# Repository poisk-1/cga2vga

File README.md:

# CGA to VGA converter

Converts RGBI/HSYNC/VSYNC TTL signal at 15 MHz pixel clock and 640 by 200 resolution to standard VGA. Prototyped on [Arty A7-35T](https://digilent.com/reference/programmable-logic/arty-a7/reference-manual?redirect=1). Production on [Cmod A7-15T](https://digilent.com/reference/programmable-logic/cmod-a7/reference-manual) board.

## Build Top.v

    $ sbt run

## Run tests

    $ sbt test

## Vivado design for Cmod A7-15T

## TODOs

- Capture alignment configurable with push buttons;
- Design PCB around Cmod A7.

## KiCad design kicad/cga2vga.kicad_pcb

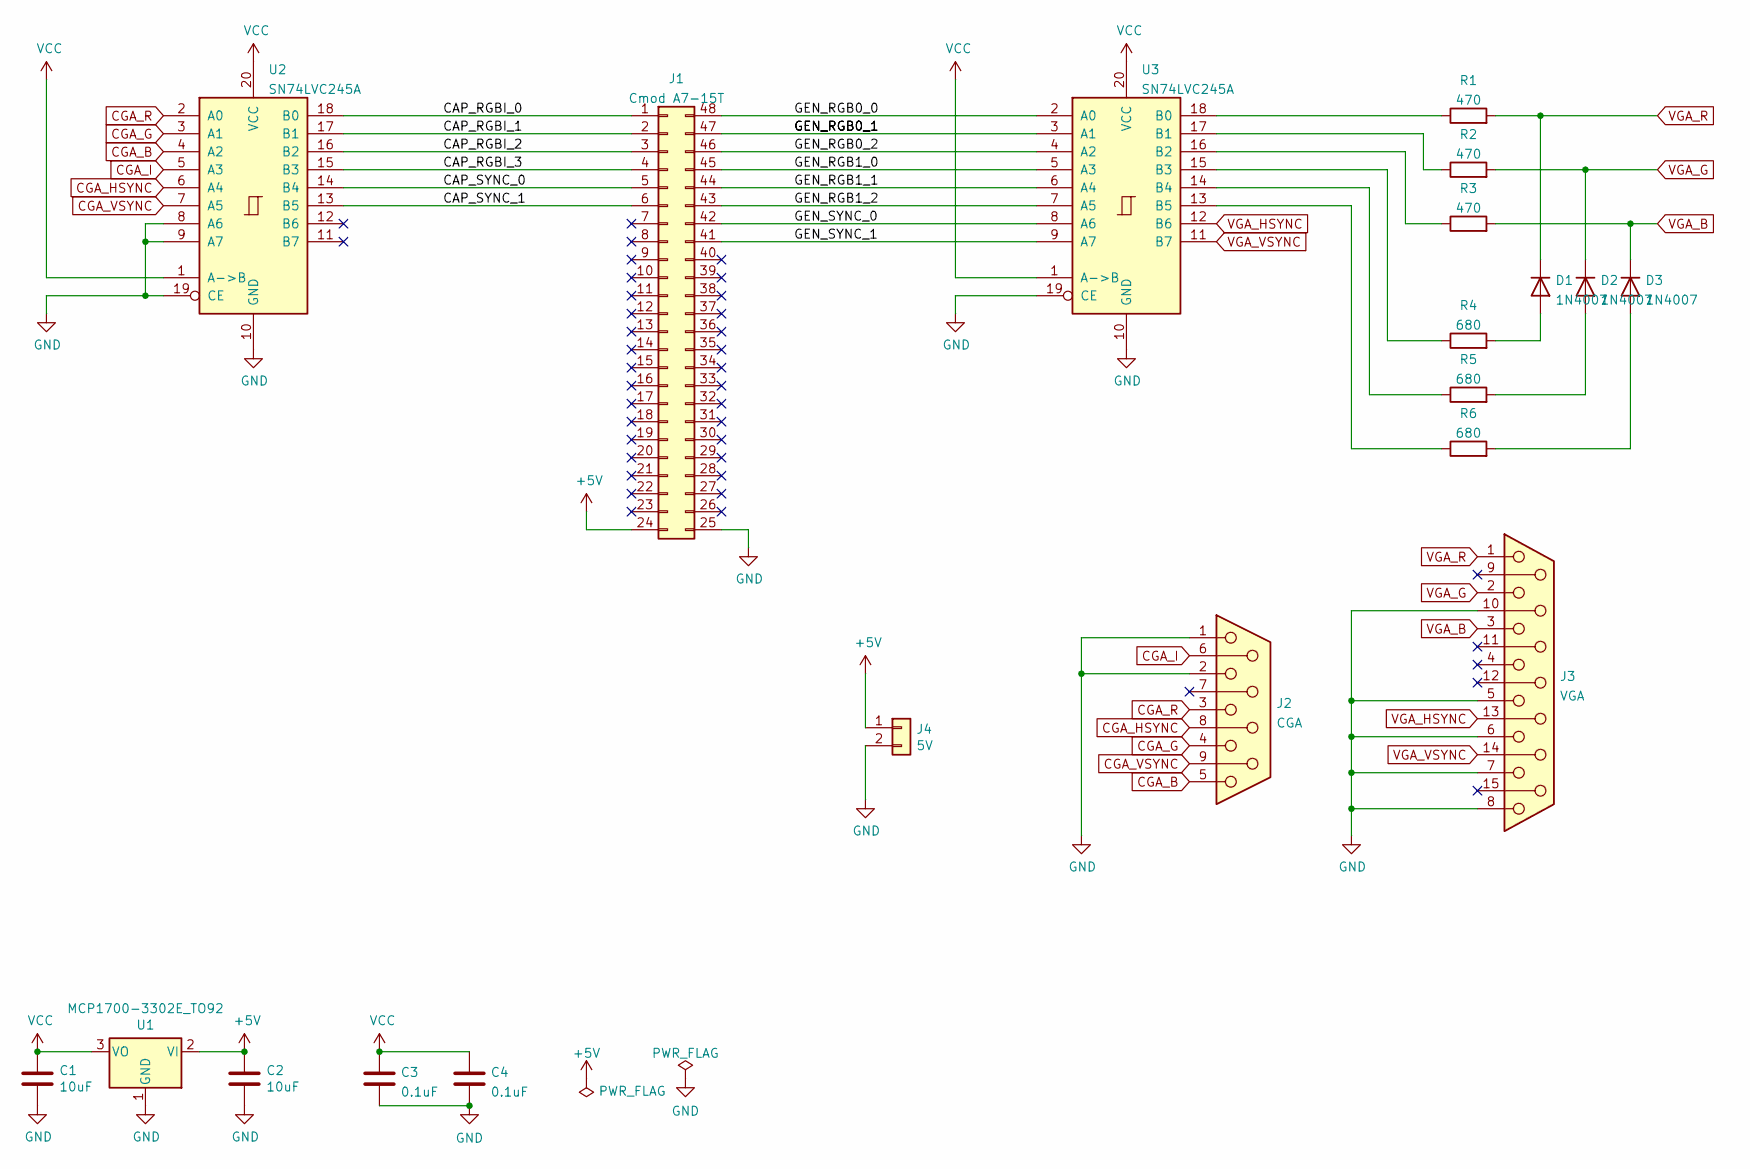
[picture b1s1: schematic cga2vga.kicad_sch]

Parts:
C1, C2: 10uF; C_Disc_D5.0mm_W2.5mm_P5.00mm
C3, C4: 0.1uF; C_Disc_D3.0mm_W1.6mm_P2.50mm
D1, D2, D3: 1N4007; D_A-405_P7.62mm_Horizontal
J1: Cmod A7-15T; DIP-48_W15.24mm_Socket
J2: CGA; LD09S13A4GX00LF
J3: VGA; L77HDE15SD1CH4F
J4: 5V; SHDR2W66P0X254_1X2_508X572X813P
R1, R2, R3: 470; R_Axial_DIN0207_L6.3mm_D2.5mm_P7.62mm_Horizontal
R4, R5, R6: 680; R_Axial_DIN0207_L6.3mm_D2.5mm_P7.62mm_Horizontal
U1: MCP1700-3302E_TO92; TO-92_HandSolder
U2, U3: SN74LVC245A; DIP-20_W7.62mm_Socket

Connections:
+5V: C2.1, J1.24, J4.1, U1.2 (VI)
/CAP_RGBI_0: J1.1, U2.18 (B0)
/CAP_RGBI_1: J1.2, U2.17 (B1)
/CAP_RGBI_2: J1.3, U2.16 (B2)
/CAP_RGBI_3: J1.4, U2.15 (B3)
/CAP_SYNC_0: J1.5, U2.14 (B4)
/CAP_SYNC_1: J1.6, U2.13 (B5)
/GEN_RGB0_0: J1.48, U3.2 (A0)
/GEN_RGB0_1: J1.47, U3.3 (A1)
/GEN_RGB0_2: J1.46, U3.4 (A2)
/GEN_RGB1_0: J1.45, U3.5 (A3)
/GEN_RGB1_1: J1.44, U3.6 (A4)
/GEN_RGB1_2: J1.43, U3.7 (A5)
/GEN_SYNC_0: J1.42, U3.8 (A6)
/GEN_SYNC_1: J1.41, U3.9 (A7)
CGA_B: J2.5, U2.4 (A2)
CGA_G: J2.4, U2.3 (A1)
CGA_HSYNC: J2.8, U2.6 (A4)
CGA_I: J2.6, U2.5 (A3)
CGA_R: J2.3, U2.2 (A0)
CGA_VSYNC: J2.9, U2.7 (A5)
GND: C1.2, C2.2, C3.2, C4.2, J1.25, J2.1, J2.2, J3.5, J3.6, J3.7, J3.8, J3.10, J4.2, U1.1 (GND), U2.8 (A6), U2.9 (A7), U2.10 (GND), U2.19 (CE), U3.10 (GND), U3.19 (CE)
unnamed: D1.2 (A), R4.2
unnamed: D2.2 (A), R5.2
unnamed: D3.2 (A), R6.2
unnamed: R1.1, U3.18 (B0)
unnamed: R2.1, U3.17 (B1)
unnamed: R3.1, U3.16 (B2)
unnamed: R4.1, U3.15 (B3)
unnamed: R5.1, U3.14 (B4)
unnamed: R6.1, U3.13 (B5)
VCC: C1.1, C3.1, C4.1, U1.3 (VO), U2.1 (A->B), U2.20 (VCC), U3.1 (A->B), U3.20 (VCC)
VGA_B: D3.1 (K), J3.3, R3.2
VGA_G: D2.1 (K), J3.2, R2.2
VGA_HSYNC: J3.13, U3.12 (B6)
VGA_R: D1.1 (K), J3.1, R1.2
VGA_VSYNC: J3.14, U3.11 (B7)

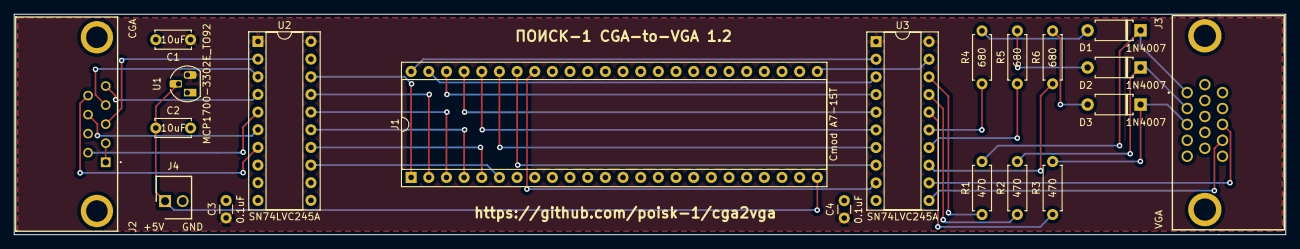
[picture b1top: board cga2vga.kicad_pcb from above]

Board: 2 copper layers, 182.9 x 31.7 mm, 20 parts (0 on the bottom side), 37 nets.

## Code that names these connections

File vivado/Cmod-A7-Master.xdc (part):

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set_property -dict { PACKAGE_PIN L3    IOSTANDARD LVCMOS33 } [get_ports { cga_green}]; #IO_L8P_T1_AD14P_35 Sch=pio[02]
set_property -dict { PACKAGE_PIN A16   IOSTANDARD LVCMOS33 } [get_ports { cga_blue  }]; #IO_L12P_T1_MRCC_16 Sch=pio[03]
set_property -dict { PACKAGE_PIN K3    IOSTANDARD LVCMOS33 } [get_ports { cga_intensity  }]; #IO_L7N_T1_AD6N_35 Sch=pio[04]
set_property -dict { PACKAGE_PIN C15   IOSTANDARD LVCMOS33 } [get_ports { cga_hsync  }]; #IO_L11P_T1_SRCC_16 Sch=pio[05]
set_property -dict { PACKAGE_PIN H1    IOSTANDARD LVCMOS33 } [get_ports { cga_vsync  }]; #IO_L3P_T0_DQS_AD5P_35 Sch=pio[06]
#set_property -dict { PACKAGE_PIN A15   IOSTANDARD LVCMOS33 } [get_ports { pio7  }]; #IO_L6N_T0_VREF_16 Sch=pio[07]
#set_property -dict { PACKAGE_PIN B15   IOSTANDARD LVCMOS33 } [get_ports { pio8  }]; #IO_L11N_T1_SRCC_16 Sch=pio[08]
#set_property -dict { PACKAGE_PIN A14   IOSTANDARD LVCMOS33 } [get_ports { pio9  }]; #IO_L6P_T0_16 Sch=pio[09]
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#set_property -dict { PACKAGE_PIN W4    IOSTANDARD LVCMOS33 } [get_ports { pio40 }]; #IO_L12N_T1_MRCC_34 Sch=pio[40]
set_property -dict { PACKAGE_PIN U5    IOSTANDARD LVCMOS33 } [get_ports { vga_v_sync }]; #IO_L16P_T2_34 Sch=pio[41]
set_property -dict { PACKAGE_PIN U2    IOSTANDARD LVCMOS33 } [get_ports { vga_h_sync }]; #IO_L9N_T1_DQS_34 Sch=pio[42]
set_property -dict { PACKAGE_PIN W6    IOSTANDARD LVCMOS33 } [get_ports { vga_b[0] }]; #IO_L13N_T2_MRCC_34 Sch=pio[43]
set_property -dict { PACKAGE_PIN U3    IOSTANDARD LVCMOS33 } [get_ports { vga_g[0] }]; #IO_L9P_T1_DQS_34 Sch=pio[44]
set_property -dict { PACKAGE_PIN U7    IOSTANDARD LVCMOS33 } [get_ports { vga_r[0] }]; #IO_L19P_T3_34 Sch=pio[45]
set_property -dict { PACKAGE_PIN W7    IOSTANDARD LVCMOS33 } [get_ports { vga_b[1] }]; #IO_L13P_T2_MRCC_34 Sch=pio[46]
set_property -dict { PACKAGE_PIN U8    IOSTANDARD LVCMOS33 } [get_ports { vga_g[1] }]; #IO_L14P_T2_SRCC_34 Sch=pio[47]
set_property -dict { PACKAGE_PIN V8    IOSTANDARD LVCMOS33 } [get_ports { vga_r[1] }]; #IO_L14N_T2_SRCC_34 Sch=pio[48]

## UART
#set_property -dict { PACKAGE_PIN J18   IOSTANDARD LVCMOS33 } [get_ports { uart_rxd_out }]; #IO_L7N_T1_D10_14 Sch=uart_rxd_out
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
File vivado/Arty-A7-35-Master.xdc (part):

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#set_property -dict { PACKAGE_PIN A9    IOSTANDARD LVCMOS33 } [get_ports { uart_txd_in }]; #IO_L14N_T2_SRCC_16 Sch=uart_txd_in

## ChipKit Outer Digital Header
set_property -dict { PACKAGE_PIN V15   IOSTANDARD LVCMOS33 } [get_ports { cga_hsync  }]; #IO_L16P_T2_CSI_B_14          Sch=ck_io[0]
set_property -dict { PACKAGE_PIN U16   IOSTANDARD LVCMOS33 } [get_ports { cga_vsync  }]; #IO_L18P_T2_A12_D28_14        Sch=ck_io[1]
set_property -dict { PACKAGE_PIN P14   IOSTANDARD LVCMOS33 } [get_ports { cga_red  }]; #IO_L8N_T1_D12_14             Sch=ck_io[2]
set_property -dict { PACKAGE_PIN T11   IOSTANDARD LVCMOS33 } [get_ports { cga_green  }]; #IO_L19P_T3_A10_D26_14        Sch=ck_io[3]
set_property -dict { PACKAGE_PIN R12   IOSTANDARD LVCMOS33 } [get_ports { cga_blue  }]; #IO_L5P_T0_D06_14             Sch=ck_io[4]
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#set_property -dict { PACKAGE_PIN P17   IOSTANDARD LVCMOS33 } [get_ports { ck_io13 }]; #IO_L12P_T1_MRCC_14           Sch=ck_io[13]

## ChipKit Inner Digital Header
set_property -dict { PACKAGE_PIN U11   IOSTANDARD LVCMOS33 } [get_ports { vga_hsync }]; #IO_L19N_T3_A09_D25_VREF_14 	Sch=ck_io[26]
set_property -dict { PACKAGE_PIN V16   IOSTANDARD LVCMOS33 } [get_ports { vga_vsync }]; #IO_L16N_T2_A15_D31_14 		Sch=ck_io[27]
set_property -dict { PACKAGE_PIN M13   IOSTANDARD LVCMOS33 } [get_ports { vga_red[0] }]; #IO_L6N_T0_D08_VREF_14 		Sch=ck_io[28]
set_property -dict { PACKAGE_PIN R10   IOSTANDARD LVCMOS33 } [get_ports { vga_red[1] }]; #IO_25_14 		 			Sch=ck_io[29]
set_property -dict { PACKAGE_PIN R11   IOSTANDARD LVCMOS33 } [get_ports { vga_green[0] }]; #IO_0_14  		 			Sch=ck_io[30]
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#set_property -dict { PACKAGE_PIN D14   IOSTANDARD LVCMOS33 } [get_ports { vaux0_p  }]; #IO_L1P_T0_AD0P_15 		Sch=ck_an_p[5]	ChipKit pin=A5
## ChipKit Outer Analog Header - as Digital I/O
## NOTE: the following constraints should be used when using these ports as digital I/O.
#set_property -dict { PACKAGE_PIN F5    IOSTANDARD LVCMOS33 } [get_ports { cga_hsync }]; #IO_0_35           	Sch=ck_a[0]		ChipKit pin=A0
#set_property -dict { PACKAGE_PIN D8    IOSTANDARD LVCMOS33 } [get_ports { cga_vsync }]; #IO_L4P_T0_35      	Sch=ck_a[1]		ChipKit pin=A1
#set_property -dict { PACKAGE_PIN C7    IOSTANDARD LVCMOS33 } [get_ports { cga_red }]; #IO_L4N_T0_35      	Sch=ck_a[2]		ChipKit pin=A2
#set_property -dict { PACKAGE_PIN E7    IOSTANDARD LVCMOS33 } [get_ports { cga_green }]; #IO_L6P_T0_35      	Sch=ck_a[3]		ChipKit pin=A3
#set_property -dict { PACKAGE_PIN D7    IOSTANDARD LVCMOS33 } [get_ports { cga_blue }]; #IO_L6N_T0_VREF_35 	Sch=ck_a[4]		ChipKit pin=A4
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
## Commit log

2021-12-27 Template cleanup
2021-12-27 Cleanup
2021-12-27 Receiver
2021-12-29 Capture video signal
2021-12-29 Frame buffer
2021-12-29 Generator
2021-12-29 Adjust naming
2021-12-30 Integrate
2021-12-30 Modify Verilog for PMOD interface
2021-12-30 Fix for low intensity
2021-12-30 Simplify
2021-12-30 Double rate capture
2022-01-01 Quad-rate capture. Align capture. Account for memory delay in generation.
2022-01-03 Symbols ROM. IOBUFs in Top to drive pins directly.
2022-01-03 Rename the project
2022-01-03 Boards
2022-01-03 License
2022-01-03 README
2022-01-03 Fix README
2022-01-03 TODOs
2022-01-22 Adapt for Cmod A7-15T
2022-01-22 Update Vivado design
2022-01-22 Adjust README
2022-02-02 Restructure for RGBI channels VGA output
2022-02-02 The PCB
2022-02-02 Fix power connector marking
2022-02-13 Fix color
2022-02-13 Ground unused inputs
2022-02-13 Valid LED
2023-01-22 Update PCB
2023-01-26 High fidelity video capture/generation
2023-01-28 Composite CGA
2023-01-29 Push button to toggle composite mode
2023-02-05 Test patterns for composite mode
2023-02-06 VGA sync generator
2023-02-10 Testbench
2023-02-12 Improve testbenches
2023-02-12 Top entity
2023-02-13 vga_color_test function
2023-02-13 Simplify vga_color_test
2023-02-13 Update schematic to reflect CMOD pin names
2023-02-13 Use GHDL in CI
2023-02-26 Check valid count
2023-04-04 CGA buffer
2023-04-04 Sampler
2023-04-04 Sync capture
2023-04-05 CGA input constraints
2023-04-21 Test and fix sync_capture
